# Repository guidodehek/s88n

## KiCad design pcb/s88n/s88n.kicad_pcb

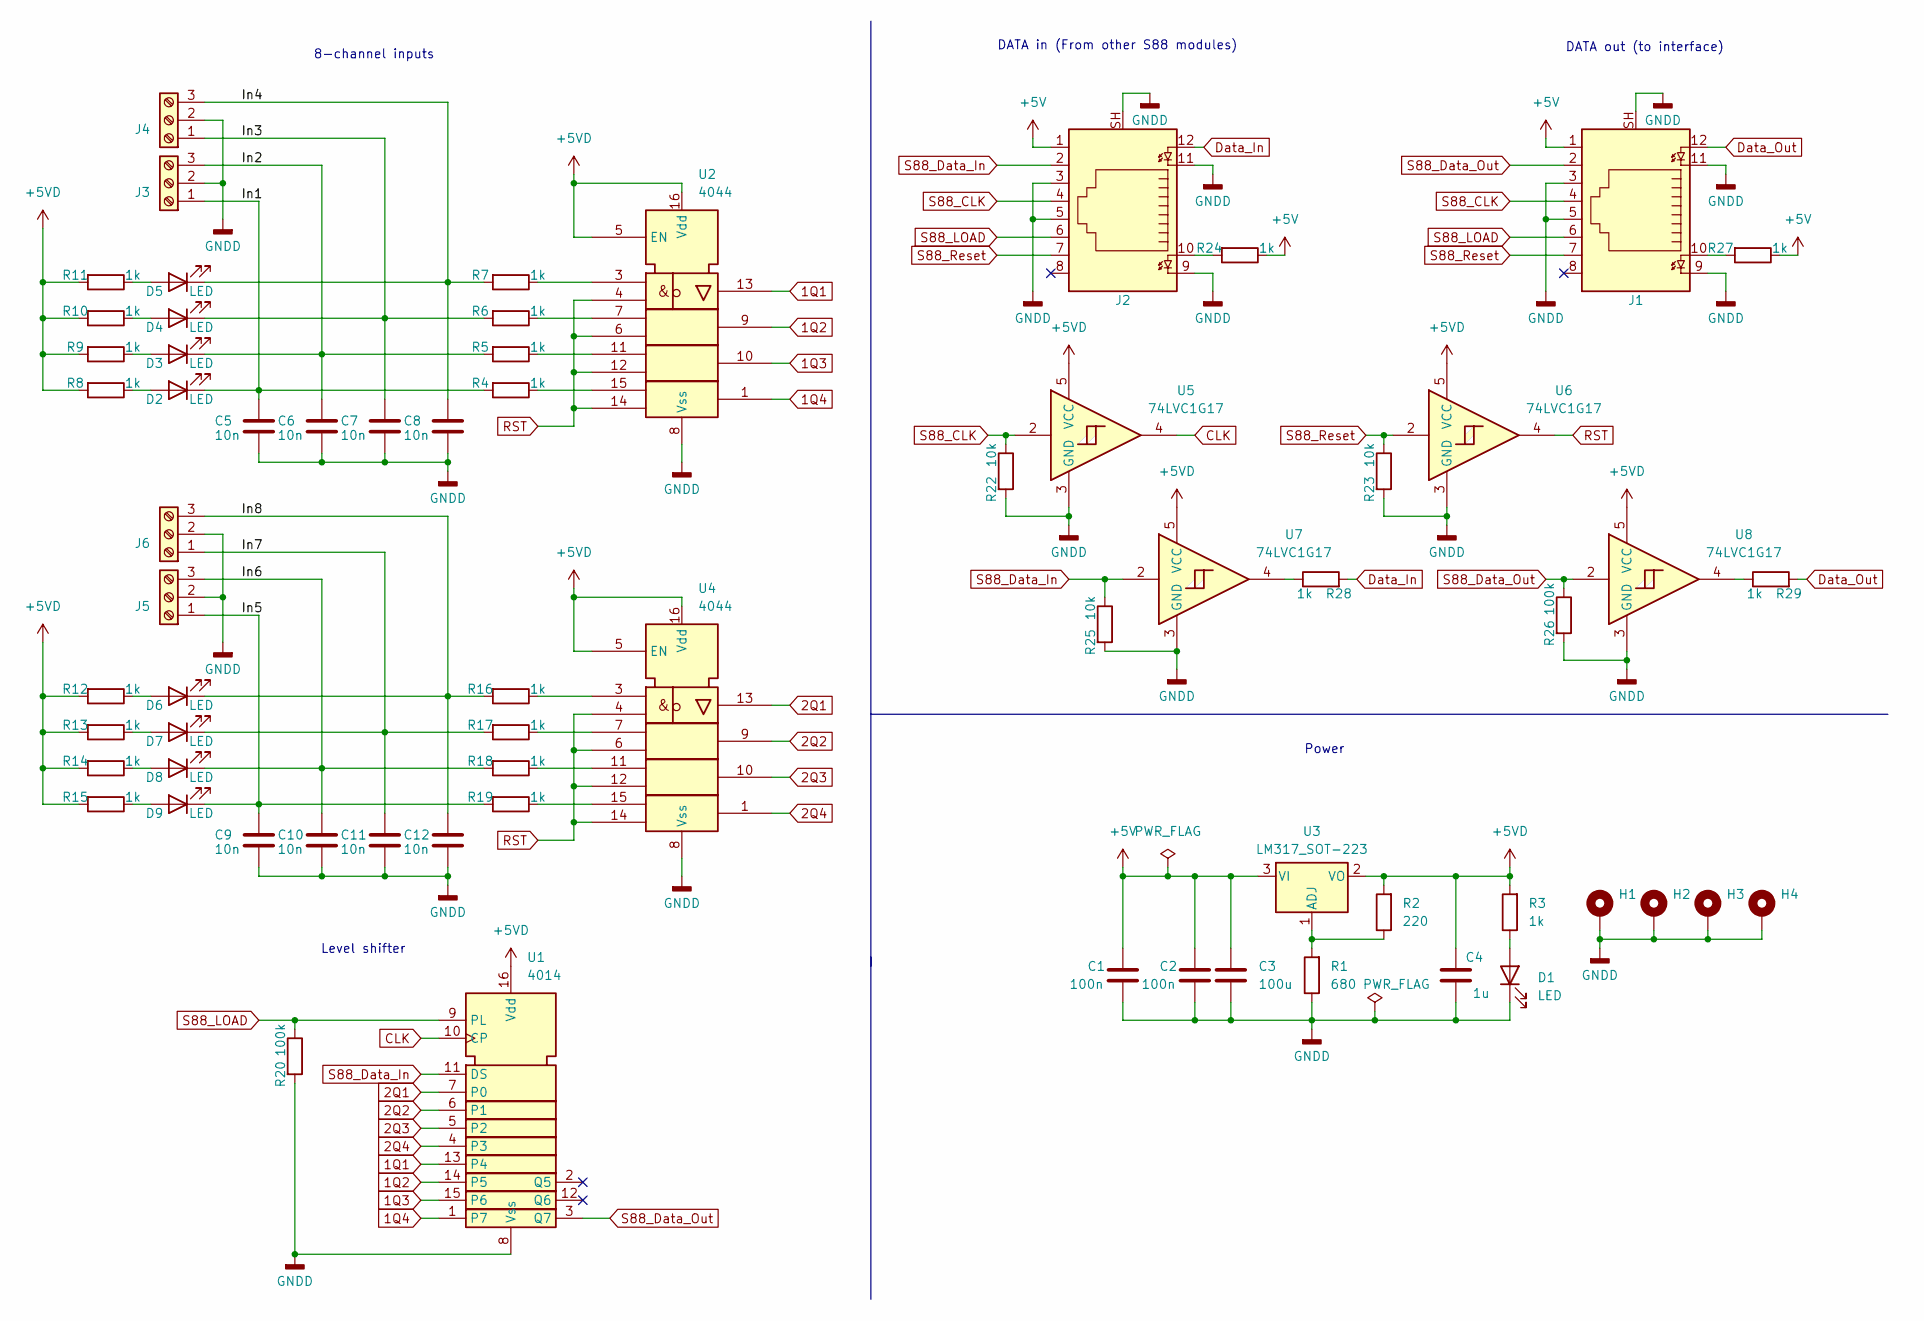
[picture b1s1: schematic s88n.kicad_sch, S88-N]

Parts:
C1, C2: 100n; C_0805_2012Metric
C3: 100u; CP_Elec_4x5.8
C4: 1u; C_0805_2012Metric
C5, C6, C7, C8, C9, C10, C11, C12: 10n; C_0805_2012Metric
D1, D2, D3, D4, D5, D6, D7, D8, D9: LED; LED_0603_1608Metric
H1, H2, H3, H4: MountingHole_Pad; MountingHole_3.2mm_M3_DIN965_Pad
J1, J2: RJ45_LED_Shielded; RJ45_Amphenol_RJHSE538X
J3, J4, J5, J6: Screw_Terminal_01x03; TerminalBlock_Xinya_XY308-2.54-3P_1x03_P2.54mm_Horizontal
R1: 680; R_0805_2012Metric
R2: 220; R_0805_2012Metric
R3, R4, R5, R6, R7, R8, R9, R10, R11, R12, R13, R14, R15, R16, R17, R18, R19, R24, R27, R28, R29: 1k; R_0805_2012Metric
R20, R26: 100k; R_0805_2012Metric
R22, R23, R25: 10k; R_0805_2012Metric
U1: 4014; SOIC-16W_7.5x10.3mm_P1.27mm
U2, U4: 4044; SOIC-16W_7.5x10.3mm_P1.27mm
U3: LM317_SOT-223; SOT-223-3_TabPin2
U5, U6, U7, U8: 74LVC1G17; SOT-23-5_HandSoldering

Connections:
1Q1: U1.13 (P4), U2.13
1Q2: U1.14 (P5), U2.9
1Q3: U1.15 (P6), U2.10
1Q4: U1.1 (P7), U2.1
2Q1: U1.7 (P0), U4.13
2Q2: U1.6 (P1), U4.9
2Q3: U1.5 (P2), U4.10
2Q4: U1.4 (P3), U4.1
+5V: C1.1, C2.1, C3.1, J1.1, J2.1, R24.1, R27.1, U3.3 (VI)
+5VD: C4.1, R2.2, R3.2, R8.2, R9.2, R10.2, R11.2, R12.2, R13.2, R14.2, R15.2, U1.16 (Vdd), U2.5 (EN), U2.16 (Vdd), U3.2 (VO), U4.5 (EN), U4.16 (Vdd), U5.5 (VCC), U6.5 (VCC), U7.5 (VCC), U8.5 (VCC)
/In1: C5.1, D2.1 (K), J3.1, R4.2
/In2: C6.1, D3.1 (K), J3.3, R5.2
/In3: C7.1, D4.1 (K), J4.1, R6.2
/In4: C8.1, D5.1 (K), J4.3, R7.2
/In5: C9.1, D9.1 (K), J5.1, R19.2
/In6: C10.1, D8.1 (K), J5.3, R18.2
/In7: C11.1, D7.1 (K), J6.1, R17.2
/In8: C12.1, D6.1 (K), J6.3, R16.2
CLK: U1.10 (CP), U5.4
Data_In: J2.12, R28.2
Data_Out: J1.12, R29.2
GNDD: C1.2, C2.2, C3.2, C4.2, C5.2, C6.2, C7.2, C8.2, C9.2, C10.2, C11.2, C12.2, D1.1 (K), H1.1, H2.1, H3.1, H4.1, J1.3, J1.5, J1.9, J1.11, J1.SH, J2.3, J2.5, J2.9, J2.11, J2.SH, J3.2, J4.2, J5.2, J6.2, R1.1, R20.2, R22.2, R23.2, R25.2, R26.2, U1.8 (Vss), U2.8 (Vss), U4.8 (Vss), U5.3 (GND), U6.3 (GND), U7.3 (GND), U8.3 (GND)
unnamed: D1.2 (A), R3.1
unnamed: D2.2 (A), R8.1
unnamed: D3.2 (A), R9.1
unnamed: D4.2 (A), R10.1
unnamed: D5.2 (A), R11.1
unnamed: D6.2 (A), R12.1
unnamed: D7.2 (A), R13.1
unnamed: D8.2 (A), R14.1
unnamed: D9.2 (A), R15.1
unnamed: J1.10, R27.2
unnamed: J2.10, R24.2
unnamed: R4.1, U2.15
unnamed: R5.1, U2.11
unnamed: R6.1, U2.7
unnamed: R7.1, U2.3
unnamed: R16.1, U4.3
unnamed: R17.1, U4.7
unnamed: R18.1, U4.11
unnamed: R19.1, U4.15
unnamed: R28.1, U7.4
unnamed: R29.1, U8.4
unnamed: R1.2, R2.1, U3.1 (ADJ)
RST: U2.4, U2.6, U2.12, U2.14, U4.4, U4.6, U4.12, U4.14, U6.4
S88_CLK: J1.4, J2.4, R22.1, U5.2
S88_Data_In: J2.2, R25.1, U1.11 (DS), U7.2
S88_Data_Out: J1.2, R26.1, U1.3 (Q7), U8.2
S88_LOAD: J1.6, J2.6, R20.1, U1.9 (PL)
S88_Reset: J1.7, J2.7, R23.1, U6.2

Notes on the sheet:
8-channel inputs
Power
DATA out (to interface)
Level shifter
DATA in (From other S88 modules)

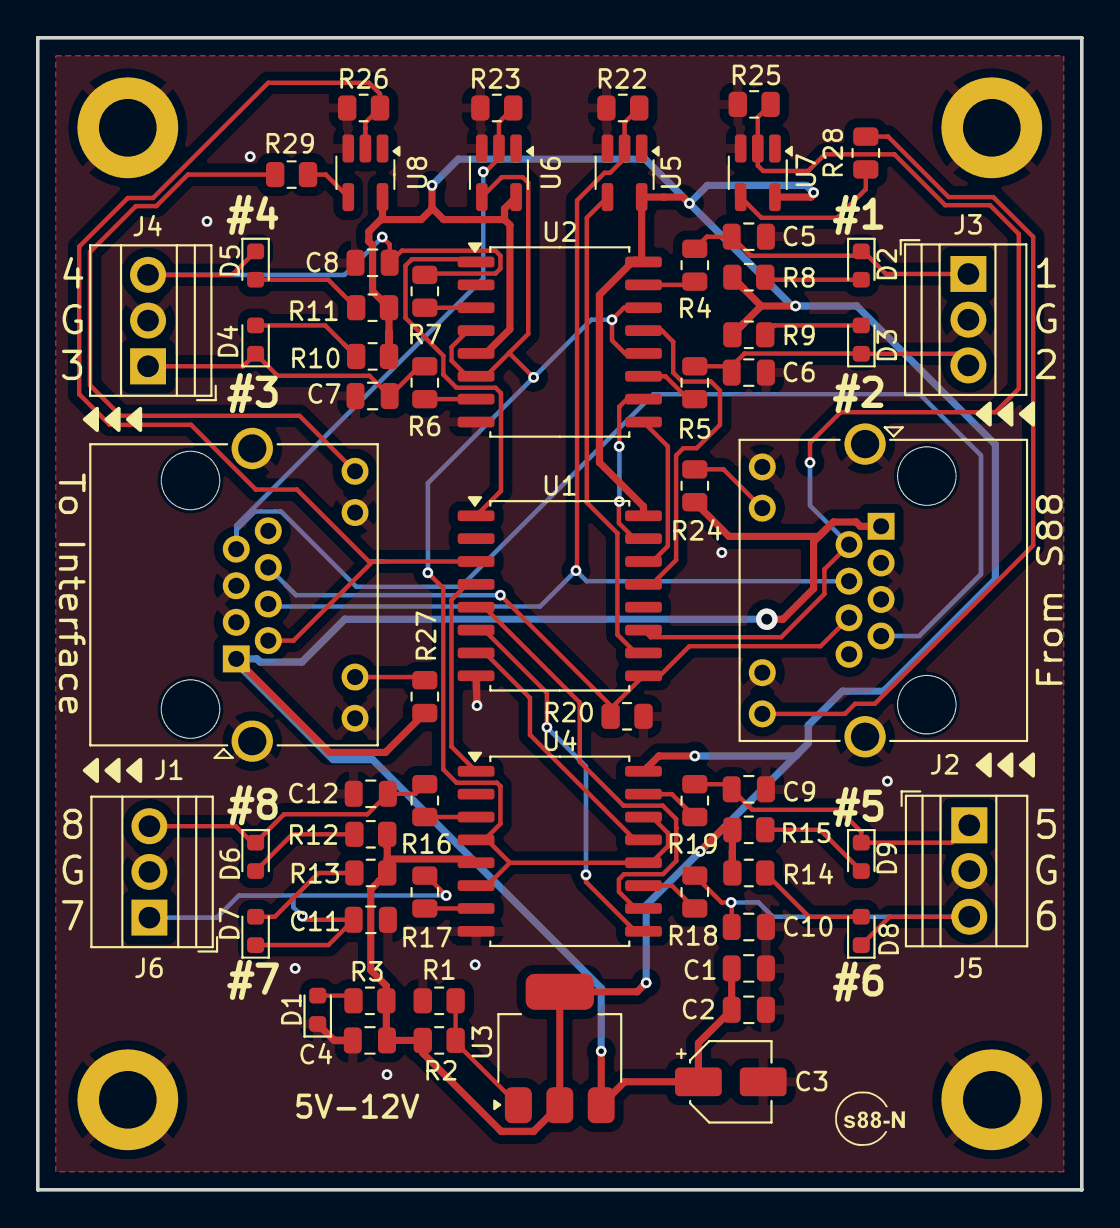
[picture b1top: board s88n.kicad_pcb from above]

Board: 2 copper layers, 58.0 x 64.0 mm, 67 parts (0 on the bottom side), 50 nets.

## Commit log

2024-05-10 feat: first schematic and board design
2024-05-10 wip: design
2024-05-11 feat: DRC OK
2024-05-11 feat: use 3 pin connectors
    wip: improve routing
2024-05-11 fix: error with data-in and data-outline
2024-05-11 feat: use rj45 leds for data line status
2024-05-11 feat: minor changes
2024-06-08 fix: resistance values of detection circuit
2024-06-09 wip: update schematic with diodetrick
